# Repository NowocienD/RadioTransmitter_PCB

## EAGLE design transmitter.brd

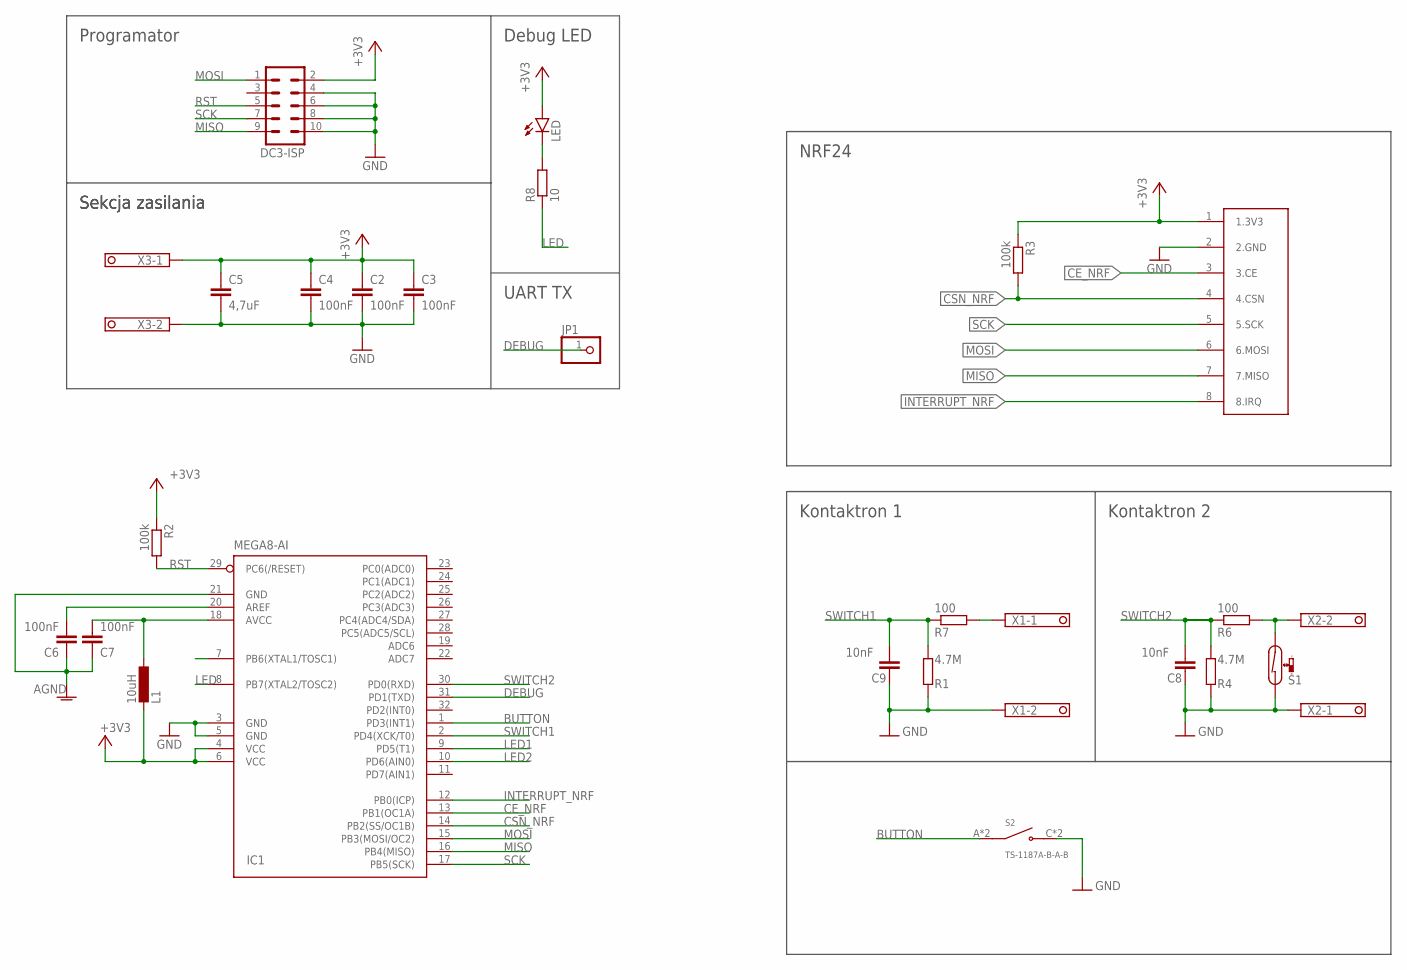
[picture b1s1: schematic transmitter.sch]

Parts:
C2, C3, C4, C6, C7: 100nF; C0805
C5: 4,7uF; C025-050X050
C8, C9: 10nF; C0805
DC3-ISP: ML10
IC1: MEGA8-AI; TQFP32-08
JP1: PINHD-1X1; 1X01
L1: 10uH; L2012C
LED: LEDCHIP-LED0805; CHIP-LED0805
R1, R4: 4.7M; M0805
R2, R3: 100k; M0805
R6, R7: 100; M0805
R8: 10; M0805
S1: REED-SWITCH-MK6-6; MK6-6
S2: TS-1187A-B-A-B; SW_TS-1187A-B-A-B
U$1: NRF24L01+
X1, X2, X3: ARK-3.5MMAPC2; 1751248

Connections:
+3V3: C2.1, C3.1, C4.1, C5.1, DC3-ISP.2, IC1.4 (VCC), IC1.6 (VCC), L1.2, LED.A, R2.1, R3.1, U$1.1 (1.3V3), X3.1
AGND: C6.1, C7.1, IC1.21 (GND)
AREF: C6.2, IC1.20 (AREF)
AVCC: C7.2, IC1.18 (AVCC), L1.1
BUTTON: IC1.1 (PD3(INT1)), S2.A (COM), S2.B (COM)
CE_NRF: IC1.13 (PB1(OC1A)), U$1.3 (3.CE)
CSN_NRF: IC1.14 (PB2(SS/OC1B)), R3.2, U$1.4 (4.CSN)
DEBUG: IC1.31 (PD1(TXD)), JP1.1
GND: C2.2, C3.2, C4.2, C5.2, C8.1, C9.1, DC3-ISP.4, DC3-ISP.6, DC3-ISP.8, DC3-ISP.10, IC1.3 (GND), IC1.5 (GND), R1.1, R4.1, S1.1, S2.C (NO), S2.D (NO), U$1.2 (2.GND), X1.2, X2.1, X3.2
INTERRUPT_NRF: IC1.12 (PB0(ICP)), U$1.8 (8.IRQ)
LED: IC1.8 (PB7(XTAL2/TOSC2)), R8.1
LED1: IC1.9 (PD5(T1))
LED2: IC1.10 (PD6(AIN0))
MISO: DC3-ISP.9, IC1.16 (PB4(MISO)), U$1.7 (7.MISO)
MOSI: DC3-ISP.1, IC1.15 (PB3(MOSI/OC2)), U$1.6 (6.MOSI)
unnamed: LED.C, R8.2
unnamed: R6.2, S1.2, X2.2
RST: DC3-ISP.5, IC1.29 (PC6(/RESET)), R2.2
SCK: DC3-ISP.7, IC1.17 (PB5(SCK)), U$1.5 (5.SCK)
SWITCH1: C9.2, IC1.2 (PD4(XCK/T0)), R1.2, R7.1
SWITCH1_WIRE: R7.2, X1.1
SWITCH2: C8.2, IC1.30 (PD0(RXD)), R4.2, R6.1

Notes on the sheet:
Kontaktron 1
Kontaktron 2
Programator
Sekcja zasilania
NRF24
Debug LED
UART TX

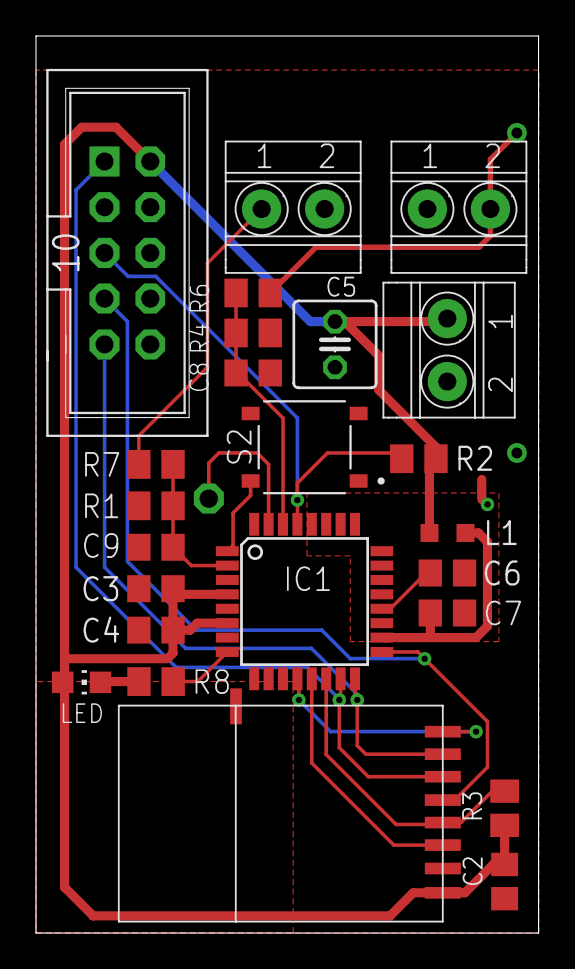
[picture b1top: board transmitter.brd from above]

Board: 2 copper layers, 27.9 x 49.8 mm, 26 parts (0 on the bottom side), 20 nets.

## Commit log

2020-11-24 do druku
2020-12-24 usuniecie masy, przestawienie led, wiekszy opis
2020-12-27 drobne poprawki
2020-12-28 dodana warstwa opisowa dla panelizacji
